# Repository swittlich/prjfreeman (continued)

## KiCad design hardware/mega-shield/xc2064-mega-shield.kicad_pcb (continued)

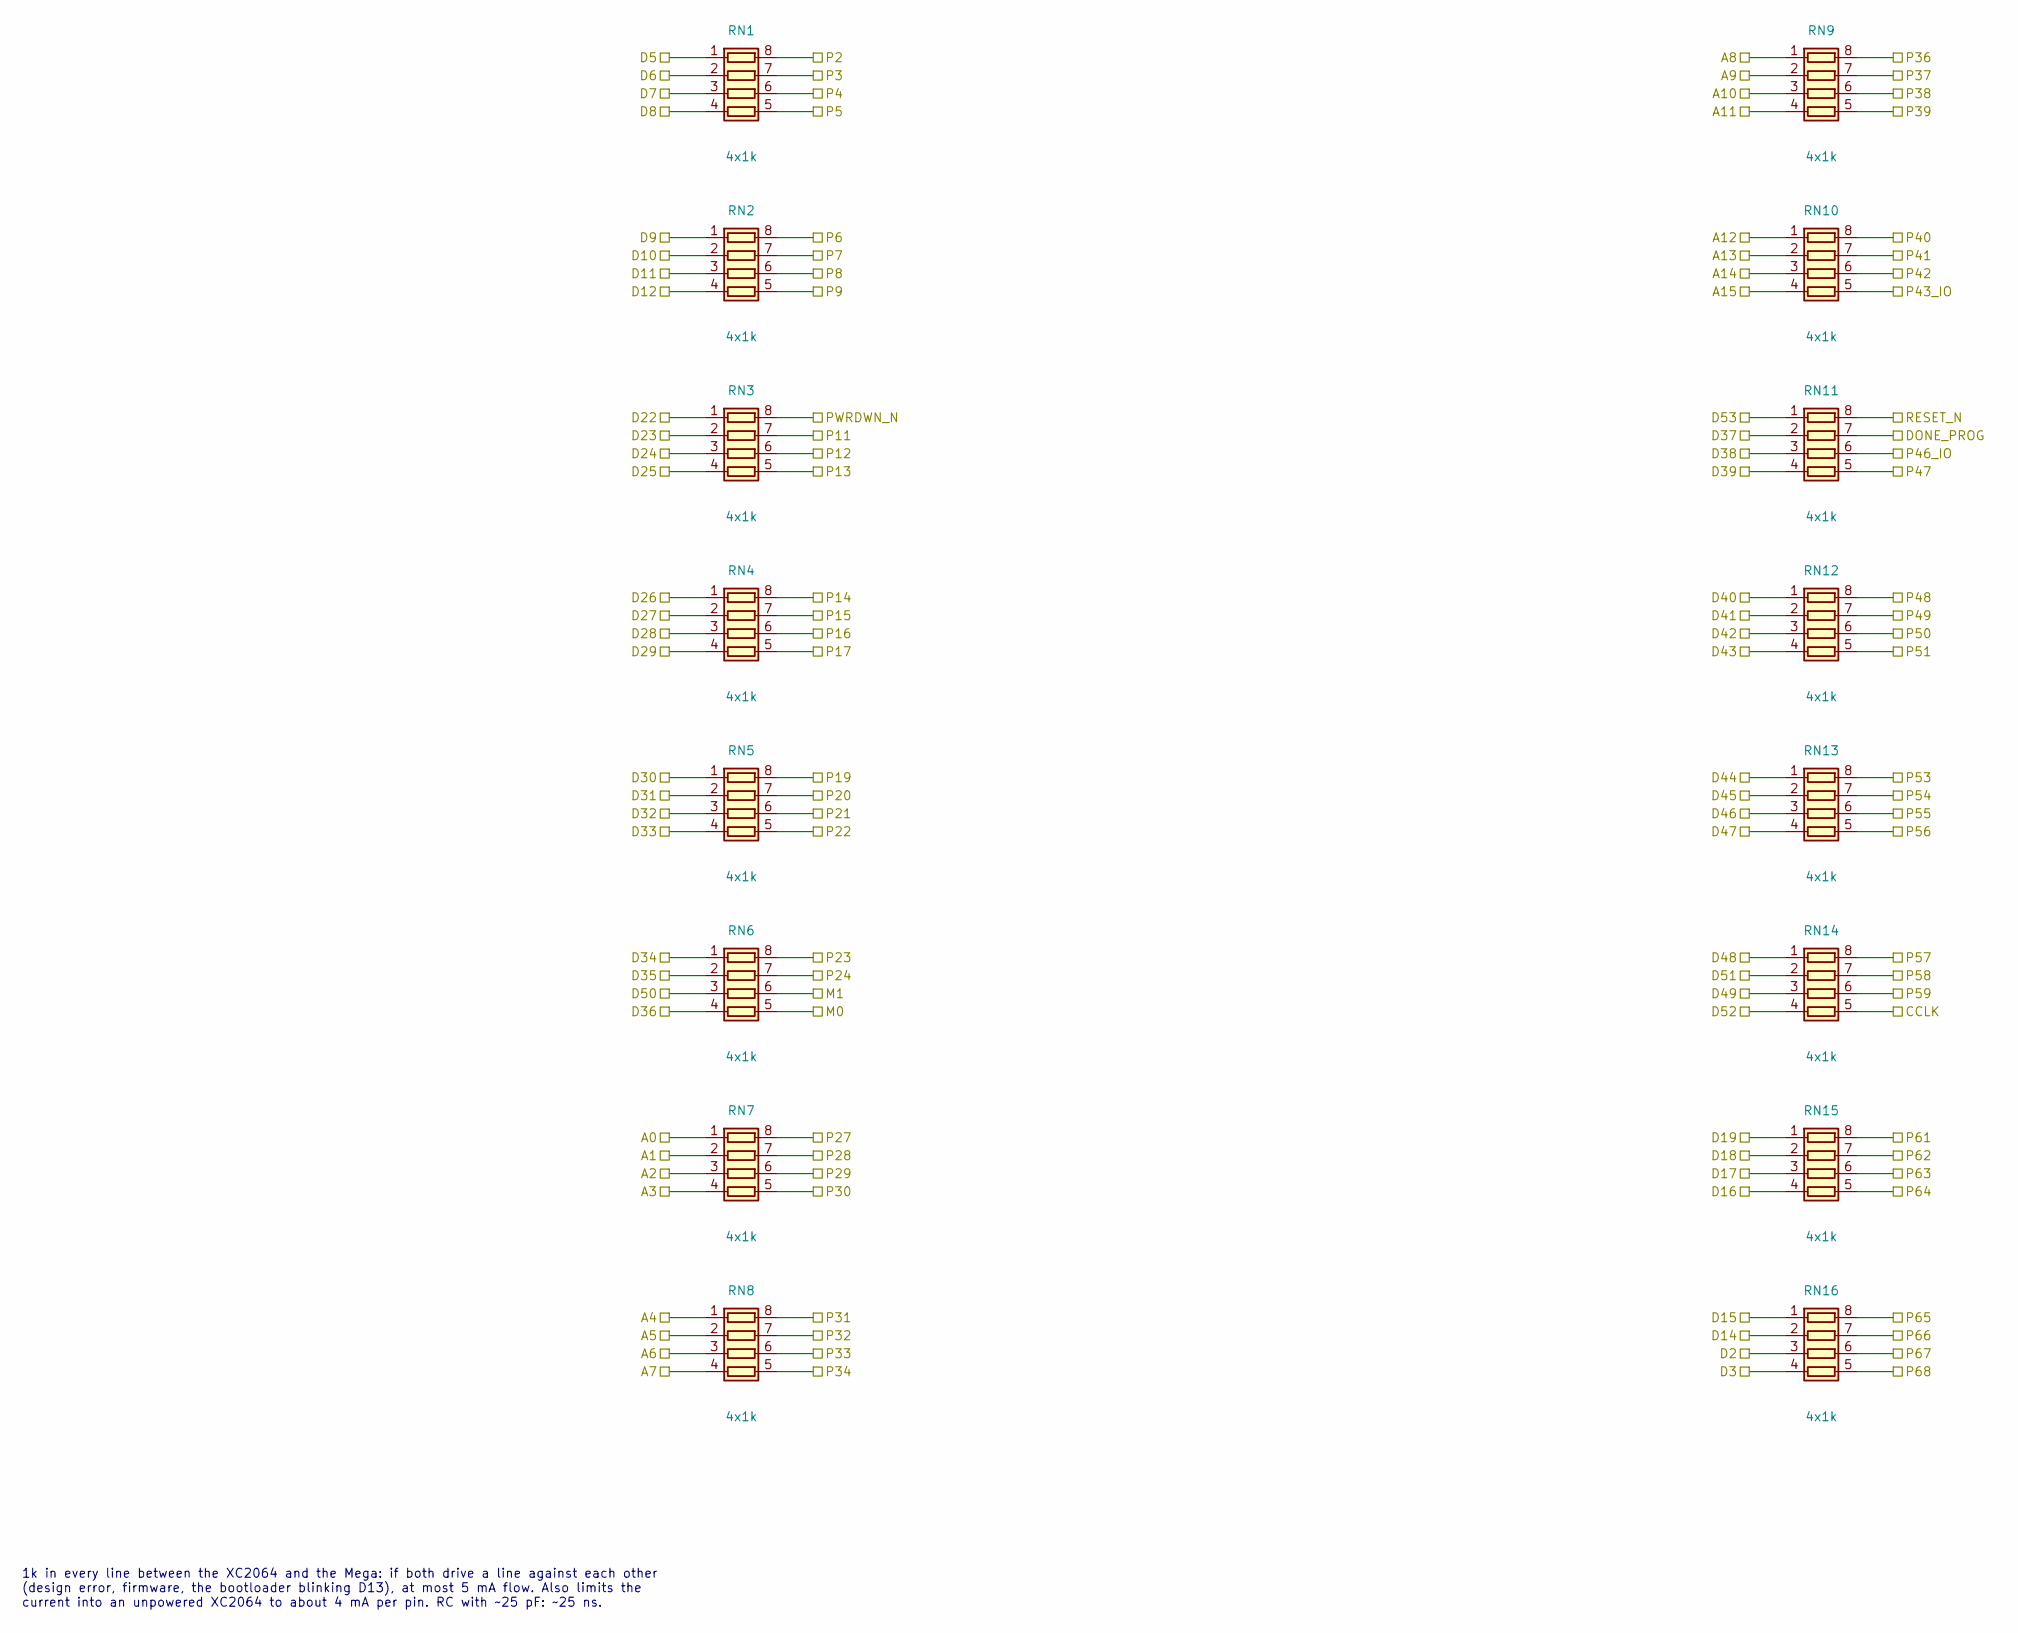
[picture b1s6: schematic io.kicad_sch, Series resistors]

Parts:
RN1, RN2, RN3, RN4, RN5, RN6, RN7, RN8, RN9, RN10, RN11, RN12, RN13, RN14, RN15, RN16: 4x1k; R_Array_Convex_4x0603; MPN 4D03WGJ0102T5E; LCSC C20197

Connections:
/A0: RN7.1 (R1.1); also elsewhere on the board
/A1: RN7.2 (R2.1); also elsewhere on the board
/A2: RN7.3 (R3.1); also elsewhere on the board
/A3: RN7.4 (R4.1); also elsewhere on the board
/A4: RN8.1 (R1.1); also elsewhere on the board
/A5: RN8.2 (R2.1); also elsewhere on the board
/A6: RN8.3 (R3.1); also elsewhere on the board
/A7: RN8.4 (R4.1); also elsewhere on the board
/A8: RN9.1 (R1.1); also elsewhere on the board
/A9: RN9.2 (R2.1); also elsewhere on the board
/A10: RN9.3 (R3.1); also elsewhere on the board
/A11: RN9.4 (R4.1); also elsewhere on the board
/A12: RN10.1 (R1.1); also elsewhere on the board
/A13: RN10.2 (R2.1); also elsewhere on the board
/A14: RN10.3 (R3.1); also elsewhere on the board
/A15: RN10.4 (R4.1); also elsewhere on the board
/CCLK: RN14.5 (R4.2); also elsewhere on the board
/D2: RN16.3 (R3.1); also elsewhere on the board
/D3: RN16.4 (R4.1); also elsewhere on the board
/D5: RN1.1 (R1.1); also elsewhere on the board
/D6: RN1.2 (R2.1); also elsewhere on the board
/D7: RN1.3 (R3.1); also elsewhere on the board
/D8: RN1.4 (R4.1); also elsewhere on the board
/D9: RN2.1 (R1.1); also elsewhere on the board
/D10: RN2.2 (R2.1); also elsewhere on the board
/D11: RN2.3 (R3.1); also elsewhere on the board
/D12: RN2.4 (R4.1); also elsewhere on the board
/D14: RN16.2 (R2.1); also elsewhere on the board
/D15: RN16.1 (R1.1); also elsewhere on the board
/D16: RN15.4 (R4.1); also elsewhere on the board
/D17: RN15.3 (R3.1); also elsewhere on the board
/D18: RN15.2 (R2.1); also elsewhere on the board
/D19: RN15.1 (R1.1); also elsewhere on the board
/D22: RN3.1 (R1.1); also elsewhere on the board
/D23: RN3.2 (R2.1); also elsewhere on the board
/D24: RN3.3 (R3.1); also elsewhere on the board
/D25: RN3.4 (R4.1); also elsewhere on the board
/D26: RN4.1 (R1.1); also elsewhere on the board
/D27: RN4.2 (R2.1); also elsewhere on the board
/D28: RN4.3 (R3.1); also elsewhere on the board
/D29: RN4.4 (R4.1); also elsewhere on the board
/D30: RN5.1 (R1.1); also elsewhere on the board
/D31: RN5.2 (R2.1); also elsewhere on the board
/D32: RN5.3 (R3.1); also elsewhere on the board
/D33: RN5.4 (R4.1); also elsewhere on the board
/D34: RN6.1 (R1.1); also elsewhere on the board
/D35: RN6.2 (R2.1); also elsewhere on the board
/D36: RN6.4 (R4.1); also elsewhere on the board
/D37: RN11.2 (R2.1); also elsewhere on the board
/D38: RN11.3 (R3.1); also elsewhere on the board
/D39: RN11.4 (R4.1); also elsewhere on the board
/D40: RN12.1 (R1.1); also elsewhere on the board
/D41: RN12.2 (R2.1); also elsewhere on the board
/D42: RN12.3 (R3.1); also elsewhere on the board
/D43: RN12.4 (R4.1); also elsewhere on the board
/D44: RN13.1 (R1.1); also elsewhere on the board
/D45: RN13.2 (R2.1); also elsewhere on the board
/D46: RN13.3 (R3.1); also elsewhere on the board
/D47: RN13.4 (R4.1); also elsewhere on the board
/D48: RN14.1 (R1.1); also elsewhere on the board
/D49: RN14.3 (R3.1); also elsewhere on the board
/D50: RN6.3 (R3.1); also elsewhere on the board
/D51: RN14.2 (R2.1); also elsewhere on the board
/D52: RN14.4 (R4.1); also elsewhere on the board
/D53: RN11.1 (R1.1); also elsewhere on the board
/DONE_PROG: RN11.7 (R2.2); also elsewhere on the board
/M0: RN6.5 (R4.2); also elsewhere on the board
/M1: RN6.6 (R3.2); also elsewhere on the board
/P2: RN1.8 (R1.2); also elsewhere on the board
/P3: RN1.7 (R2.2); also elsewhere on the board
/P4: RN1.6 (R3.2); also elsewhere on the board
/P5: RN1.5 (R4.2); also elsewhere on the board
/P6: RN2.8 (R1.2); also elsewhere on the board
/P7: RN2.7 (R2.2); also elsewhere on the board
/P8: RN2.6 (R3.2); also elsewhere on the board
/P9: RN2.5 (R4.2); also elsewhere on the board
/P11: RN3.7 (R2.2); also elsewhere on the board
/P12: RN3.6 (R3.2); also elsewhere on the board
/P13: RN3.5 (R4.2); also elsewhere on the board
/P14: RN4.8 (R1.2); also elsewhere on the board
/P15: RN4.7 (R2.2); also elsewhere on the board
/P16: RN4.6 (R3.2); also elsewhere on the board
/P17: RN4.5 (R4.2); also elsewhere on the board
/P19: RN5.8 (R1.2); also elsewhere on the board
/P20: RN5.7 (R2.2); also elsewhere on the board
/P21: RN5.6 (R3.2); also elsewhere on the board
/P22: RN5.5 (R4.2); also elsewhere on the board
/P23: RN6.8 (R1.2); also elsewhere on the board
/P24: RN6.7 (R2.2); also elsewhere on the board
/P27: RN7.8 (R1.2); also elsewhere on the board
/P28: RN7.7 (R2.2); also elsewhere on the board
/P29: RN7.6 (R3.2); also elsewhere on the board
/P30: RN7.5 (R4.2); also elsewhere on the board
/P31: RN8.8 (R1.2); also elsewhere on the board
/P32: RN8.7 (R2.2); also elsewhere on the board
/P33: RN8.6 (R3.2); also elsewhere on the board
/P34: RN8.5 (R4.2); also elsewhere on the board
/P36: RN9.8 (R1.2); also elsewhere on the board
/P37: RN9.7 (R2.2); also elsewhere on the board
/P38: RN9.6 (R3.2); also elsewhere on the board
/P39: RN9.5 (R4.2); also elsewhere on the board
/P40: RN10.8 (R1.2); also elsewhere on the board
/P41: RN10.7 (R2.2); also elsewhere on the board
/P42: RN10.6 (R3.2); also elsewhere on the board
/P43_IO: RN10.5 (R4.2); also elsewhere on the board
/P46_IO: RN11.6 (R3.2); also elsewhere on the board
/P47: RN11.5 (R4.2); also elsewhere on the board
/P48: RN12.8 (R1.2); also elsewhere on the board
/P49: RN12.7 (R2.2); also elsewhere on the board
/P50: RN12.6 (R3.2); also elsewhere on the board
/P51: RN12.5 (R4.2); also elsewhere on the board
/P53: RN13.8 (R1.2); also elsewhere on the board
/P54: RN13.7 (R2.2); also elsewhere on the board
/P55: RN13.6 (R3.2); also elsewhere on the board
/P56: RN13.5 (R4.2); also elsewhere on the board
/P57: RN14.8 (R1.2); also elsewhere on the board
/P58: RN14.7 (R2.2); also elsewhere on the board
/P59: RN14.6 (R3.2); also elsewhere on the board
/P61: RN15.8 (R1.2); also elsewhere on the board
/P62: RN15.7 (R2.2); also elsewhere on the board
/P63: RN15.6 (R3.2); also elsewhere on the board
/P64: RN15.5 (R4.2); also elsewhere on the board
/P65: RN16.8 (R1.2); also elsewhere on the board
/P66: RN16.7 (R2.2); also elsewhere on the board
/P67: RN16.6 (R3.2); also elsewhere on the board
/P68: RN16.5 (R4.2); also elsewhere on the board
/PWRDWN_N: RN3.8 (R1.2); also elsewhere on the board
/RESET_N: RN11.8 (R1.2); also elsewhere on the board

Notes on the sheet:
1k in every line between the XC2064 and the Mega: if both drive a line against each other (design error, firmware, the bootloader blinking D13), at most 5 mA flow. Also limits the current into an unpowered XC2064 to about 4 mA per pin. RC with ~25 pF: ~25 ns.

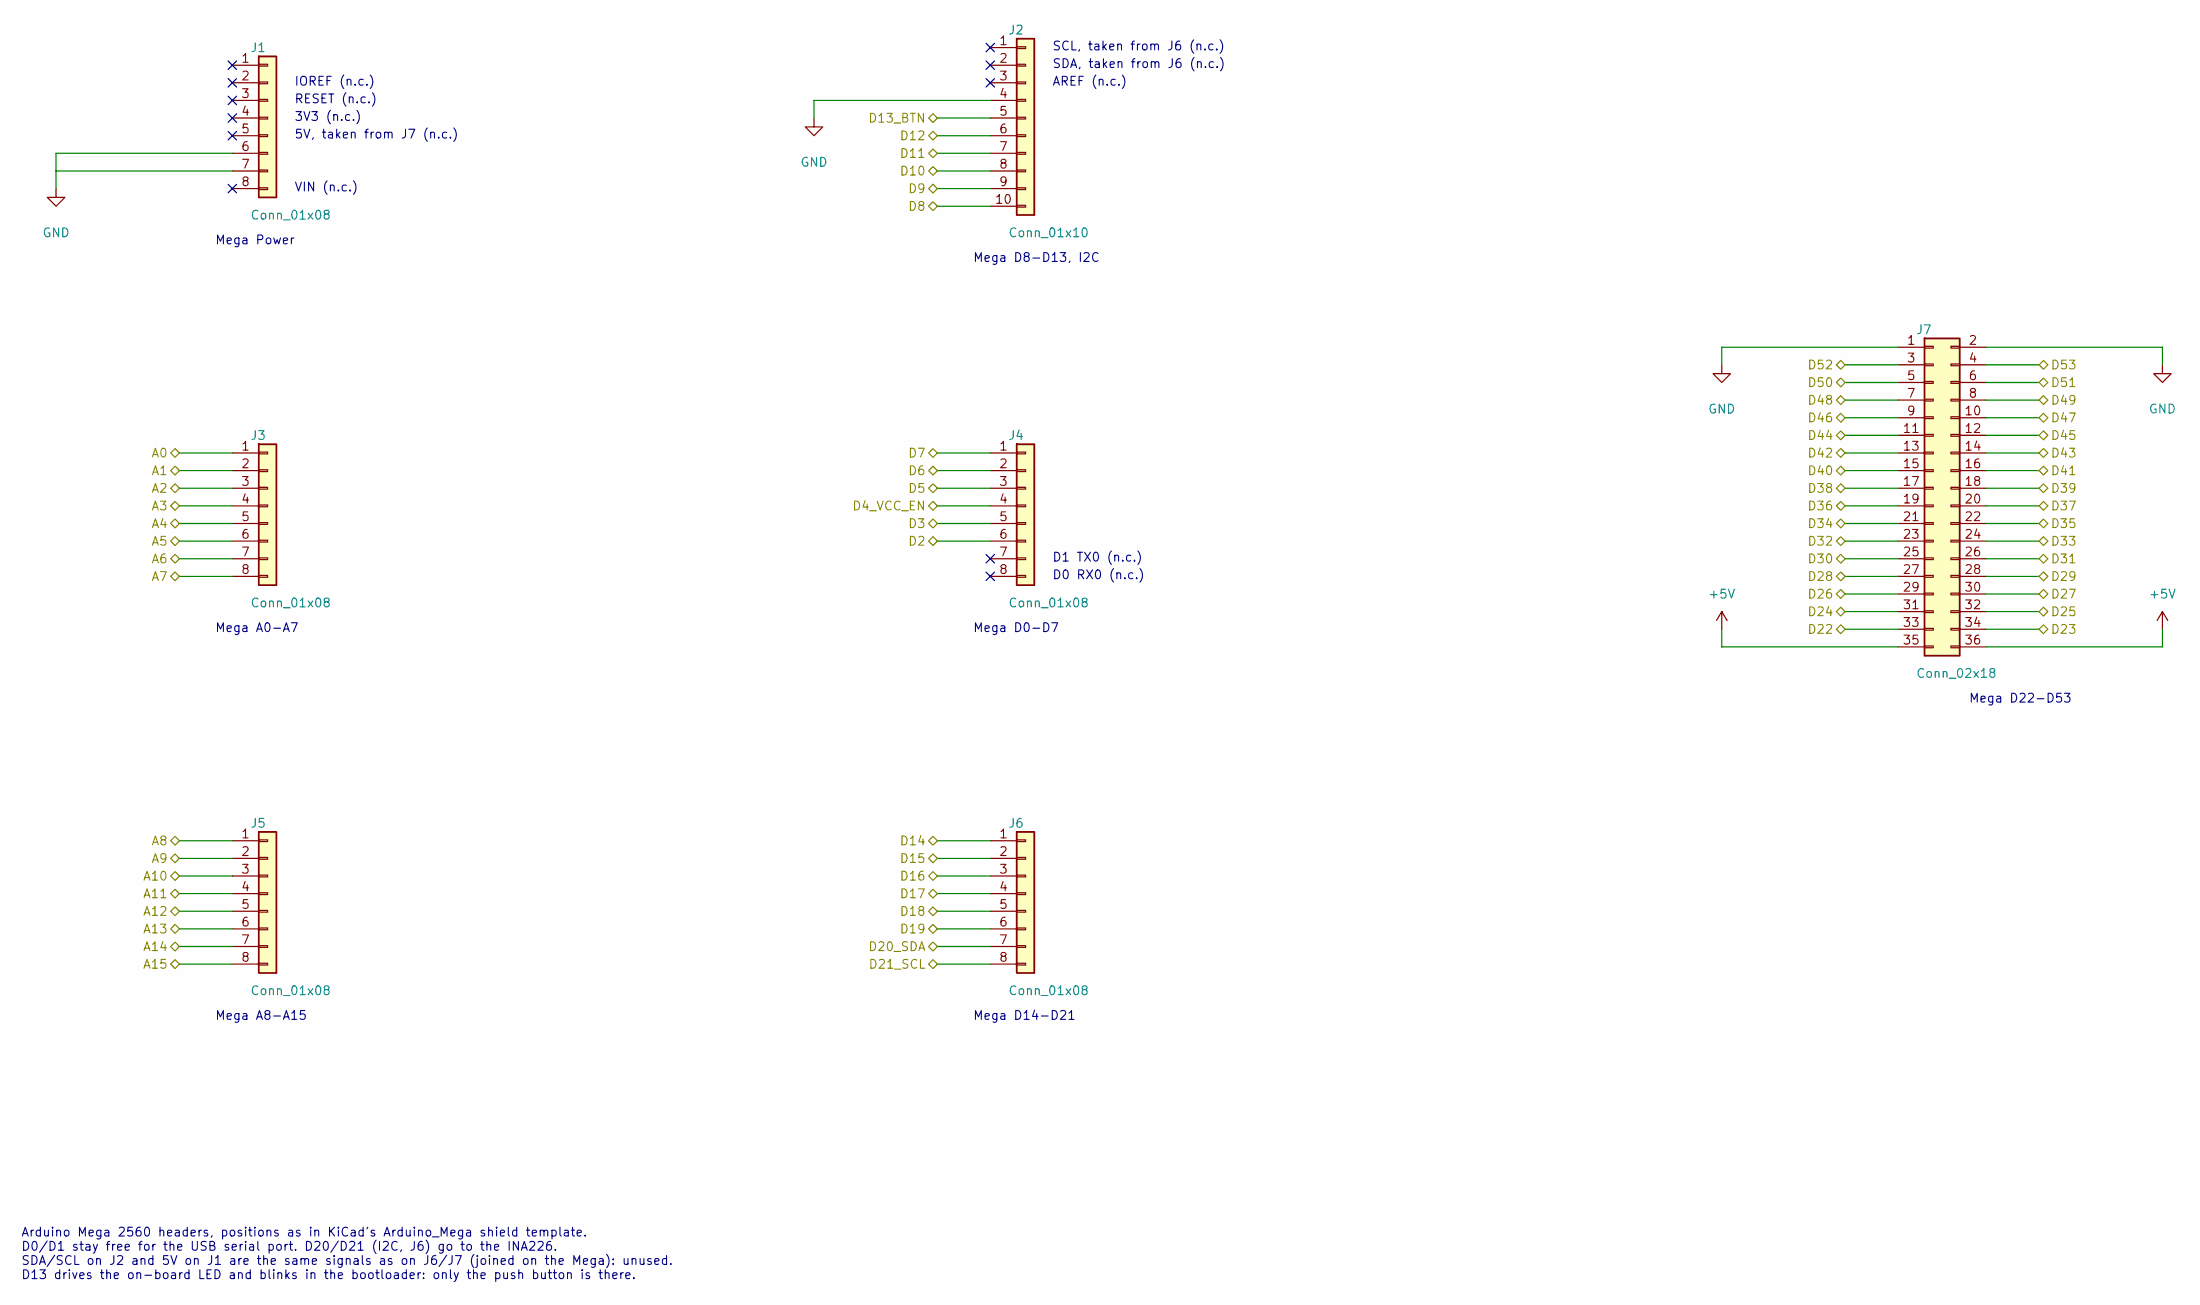
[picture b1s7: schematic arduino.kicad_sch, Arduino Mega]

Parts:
J1, J3, J4, J5, J6: Conn_01x08; PinHeader_1x08_P2.54mm_Vertical; MPN PZ254V-11-08P; LCSC C492407
J2: Conn_01x10; PinHeader_1x10_P2.54mm_Vertical; MPN PZ254V-11-10P; LCSC C492409
J7: Conn_02x18; PinHeader_2x18_P2.54mm_Vertical; MPN PZ254V-12-36P; LCSC C22465942

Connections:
+5V: J7.35, J7.36; also elsewhere on the board
/A0: J3.1; also elsewhere on the board
/A1: J3.2; also elsewhere on the board
/A2: J3.3; also elsewhere on the board
/A3: J3.4; also elsewhere on the board
/A4: J3.5; also elsewhere on the board
/A5: J3.6; also elsewhere on the board
/A6: J3.7; also elsewhere on the board
/A7: J3.8; also elsewhere on the board
/A8: J5.1; also elsewhere on the board
/A9: J5.2; also elsewhere on the board
/A10: J5.3; also elsewhere on the board
/A11: J5.4; also elsewhere on the board
/A12: J5.5; also elsewhere on the board
/A13: J5.6; also elsewhere on the board
/A14: J5.7; also elsewhere on the board
/A15: J5.8; also elsewhere on the board
/D2: J4.6; also elsewhere on the board
/D3: J4.5; also elsewhere on the board
/D4_VCC_EN: J4.4; also elsewhere on the board
/D5: J4.3; also elsewhere on the board
/D6: J4.2; also elsewhere on the board
/D7: J4.1; also elsewhere on the board
/D8: J2.10; also elsewhere on the board
/D9: J2.9; also elsewhere on the board
/D10: J2.8; also elsewhere on the board
/D11: J2.7; also elsewhere on the board
/D12: J2.6; also elsewhere on the board
/D13_BTN: J2.5; also elsewhere on the board
/D14: J6.1; also elsewhere on the board
/D15: J6.2; also elsewhere on the board
/D16: J6.3; also elsewhere on the board
/D17: J6.4; also elsewhere on the board
/D18: J6.5; also elsewhere on the board
/D19: J6.6; also elsewhere on the board
/D20_SDA: J6.7; also elsewhere on the board
/D21_SCL: J6.8; also elsewhere on the board
/D22: J7.33; also elsewhere on the board
/D23: J7.34; also elsewhere on the board
/D24: J7.31; also elsewhere on the board
/D25: J7.32; also elsewhere on the board
/D26: J7.29; also elsewhere on the board
/D27: J7.30; also elsewhere on the board
/D28: J7.27; also elsewhere on the board
/D29: J7.28; also elsewhere on the board
/D30: J7.25; also elsewhere on the board
/D31: J7.26; also elsewhere on the board
/D32: J7.23; also elsewhere on the board
/D33: J7.24; also elsewhere on the board
/D34: J7.21; also elsewhere on the board
/D35: J7.22; also elsewhere on the board
/D36: J7.19; also elsewhere on the board
/D37: J7.20; also elsewhere on the board
/D38: J7.17; also elsewhere on the board
/D39: J7.18; also elsewhere on the board
/D40: J7.15; also elsewhere on the board
/D41: J7.16; also elsewhere on the board
/D42: J7.13; also elsewhere on the board
/D43: J7.14; also elsewhere on the board
/D44: J7.11; also elsewhere on the board
/D45: J7.12; also elsewhere on the board
/D46: J7.9; also elsewhere on the board
/D47: J7.10; also elsewhere on the board
/D48: J7.7; also elsewhere on the board
/D49: J7.8; also elsewhere on the board
/D50: J7.5; also elsewhere on the board
/D51: J7.6; also elsewhere on the board
/D52: J7.3; also elsewhere on the board
/D53: J7.4; also elsewhere on the board
GND: J1.6, J1.7, J2.4, J7.1, J7.2; also elsewhere on the board

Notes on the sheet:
Mega D0-D7
VIN (n.c.)
RESET (n.c.)
AREF (n.c.)
Arduino Mega 2560 headers, positions as in KiCad's Arduino_Mega shield template. D0/D1 stay free for the USB serial port. D20/D21 (I2C, J6) go to the INA226. SDA/SCL on J2 and 5V on J1 are the same signals as on J6/J7 (joined on the Mega): unused. D13 drives the on-board LED and blinks in the bootl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
Mega D8-D13, I2C
Mega D22-D53
3V3 (n.c.)
Mega Power
Mega D14-D21
5V, taken from J7 (n.c.)
Mega A0-A7
D0 RX0 (n.c.)
SDA, taken from J6 (n.c.)
D1 TX0 (n.c.)
SCL, taken from J6 (n.c.)
IOREF (n.c.)
Mega A8-A15

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
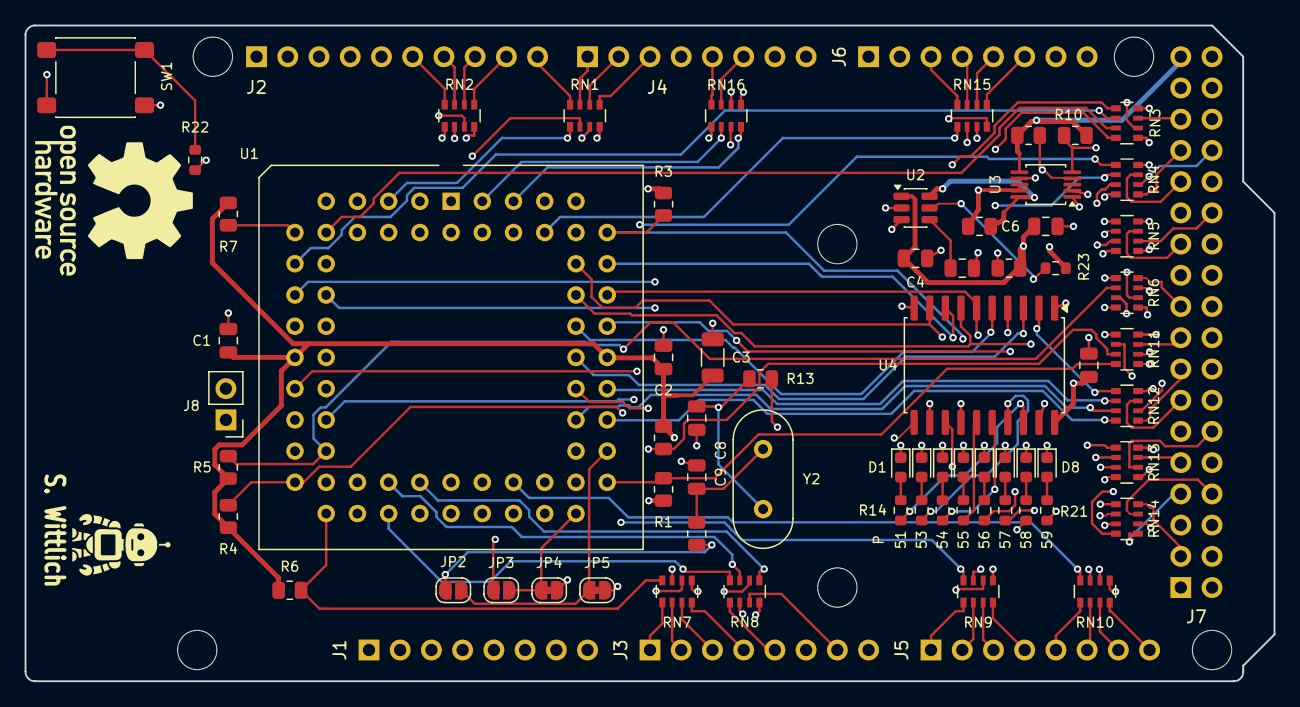
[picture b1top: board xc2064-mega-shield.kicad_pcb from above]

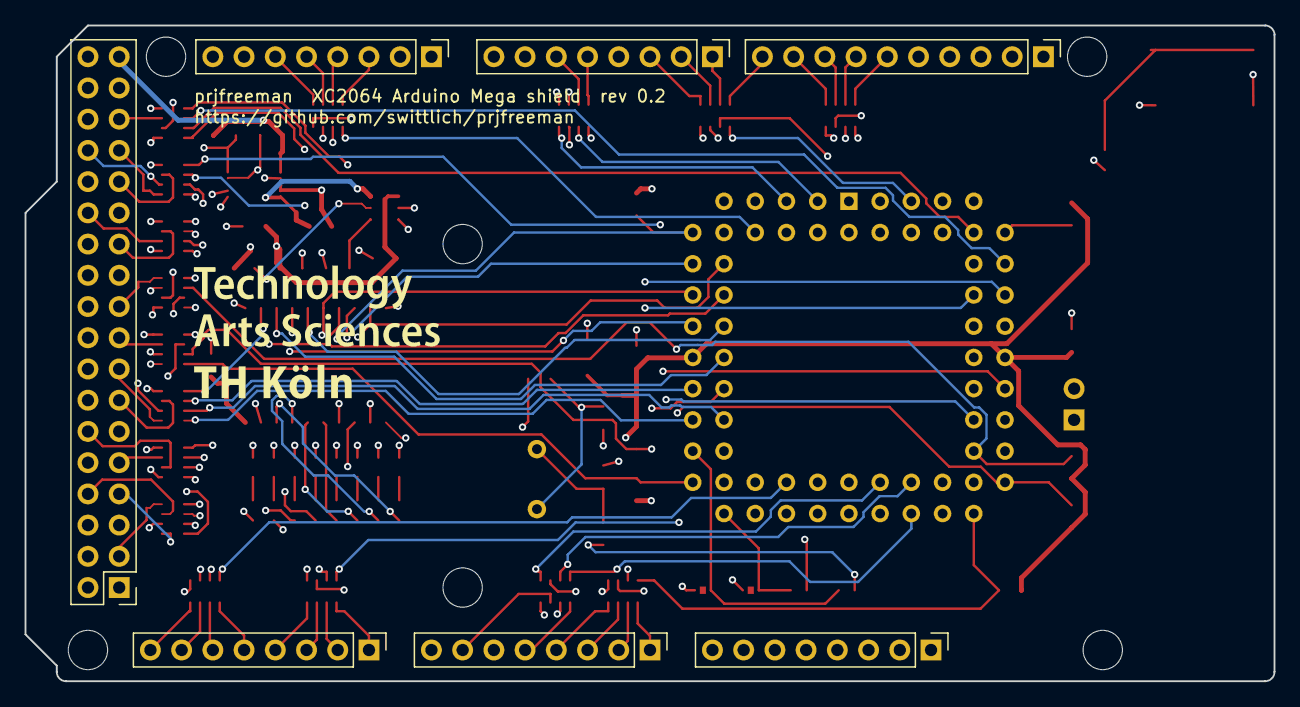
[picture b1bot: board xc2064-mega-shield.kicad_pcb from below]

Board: 4 copper layers, 101.6 x 53.3 mm, 84 parts (8 on the bottom side), 160 nets.

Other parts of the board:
MH1, MH2, MH3, MH4, MH5, MH6: MountingHole_3.2mm
